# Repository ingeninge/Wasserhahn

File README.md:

# Wasserhahn

ATTENTION! This repository is only for testing! No production, and never will be.

MQTT controlled Motor Bulb Valve ESP8266 Arduino

Manufactor is END. Here is a link to the Datasheet: https://shop.end.de/armaturen/antriebe-und-zubehoer/elektrische-antriebe/ne034100-elektrischer-schwenkantrieb-30nm-230v-ac

Since my water tap in the garden was leaking and the repair would have included ripping down the building bricks, I asked a friend to build in a ball valve. 
On this I could mount a motor to open and close the garden water tap.
To control the motor I use a ESP8266-12 (WROOM-02) and two relays. The ESP uses 2 Inputs and 2 Outputs.
The schematic can be found in the folder images.
The Inputs are from the auxiliary isolated contacts from the motor. The contacts are closed ONLY at the end position of each turn.br>If both are open the valve is in between open and close.
The Outputs are controlling two relays. One for opening and one for closing the valve. The outputs are held active for 90 seconds.
<br>MQTT- protocol is used to control the garden water tap remotely.
First idea was to let it work with an Arduino Sketch, witch you can find in the sources. But then I figured out how to set up Tasmota to work with this Board and Motor. The workaround is: Tasmota [https://github.com/arendst/Tasmota] (I use Version 7.1) controls 2 relays - one for Opening and one for Closing the tap. The downside is, you will have to use two buttons or configure node-red with a function to control the state and switch between the states.<br>
For Programming see https://www.forward.com.au/pfod/ESP8266/GPIOpins/index.html GPIO0 and RST are on Jumper J5. GPIO2 is permanently pulled up via R8.
Todo: Remove copper under the antenna! Enable access to GPIO15 for programming mode or pull low permanent. update mill and drill files, mill, solder and test the layout. Release to public

The settings for Tasmota can be found in the Wiki https://github.com/ingeninge/Wasserhahn/wiki

BTW: I can control the bulb valve with a remote control in the garden, so I don't have to pull out my mobile to open the tap. [Remote control for Wasserhahn](https://github.com/ingeninge/ESP-Watertap-Remote)

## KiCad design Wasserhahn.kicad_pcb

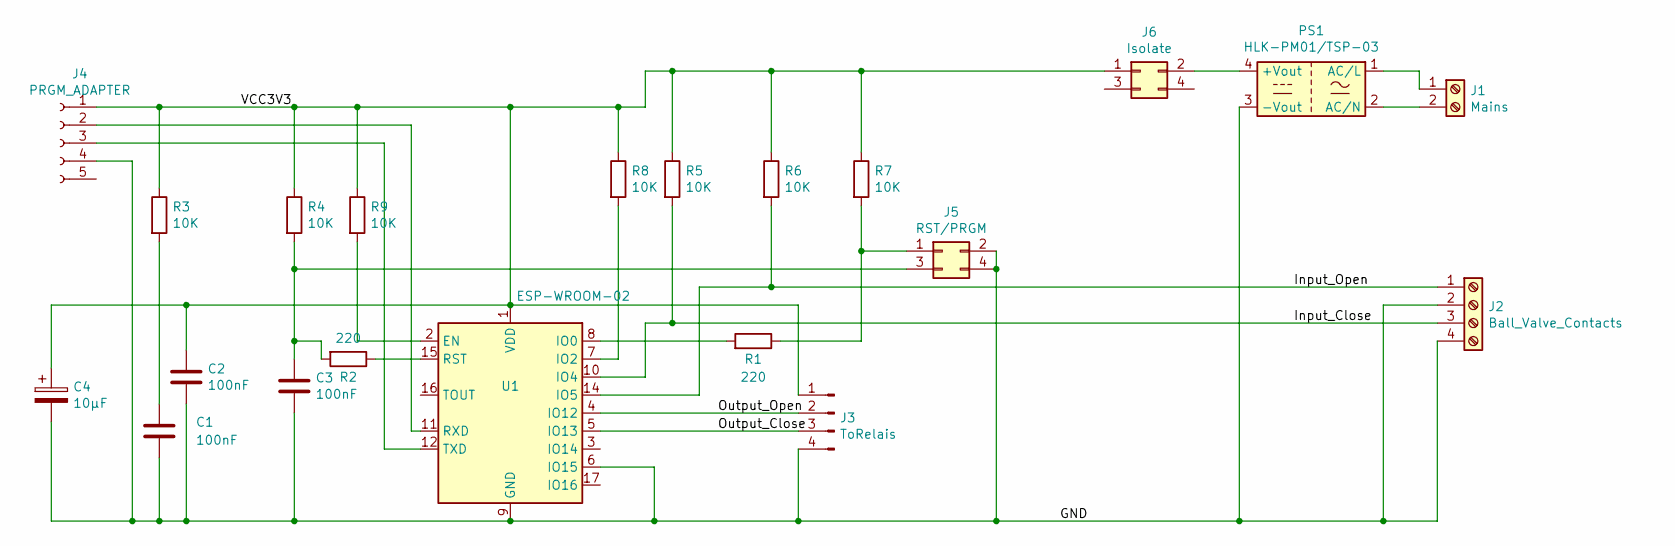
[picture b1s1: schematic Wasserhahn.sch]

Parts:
C1, C2, C3: 100nF; CP_Radial_D4.0mm_P2.00mm
C4: 10µF; CP_Radial_D6.3mm_P2.50mm
J1: Mains; TerminalBlock_Phoenix_PT-1,5-2-5.0-H_1x02_P5.00mm_Horizontal
J2: Ball_Valve_Contacts; TerminalBlock_Phoenix_PT-1,5-4-5.0-H_1x04_P5.00mm_Horizontal
J3: ToRelais; PinHeader_1x04_P2.54mm_Vertical
J4: PRGM_ADAPTER; PinHeader_1x05_P2.54mm_Vertical
J5: RST/PRGM; PinHeader_2x02_P2.54mm_Vertical
J6: Isolate; PinHeader_2x02_P2.54mm_Vertical
PS1: HLK-PM01/TSP-03; Converter_ACDC_HiLink_HLK-PMxx
R1, R2: 220; R_Axial_DIN0207_L6.3mm_D2.5mm_P10.16mm_Horizontal
R3, R4, R5, R6, R7, R8, R9: 10K; R_Axial_DIN0207_L6.3mm_D2.5mm_P10.16mm_Horizontal
U1: ESP-WROOM-02

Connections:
/GND: C1.2, C2.2, C3.2, C4.2, J2.2, J2.4, J3.4, J4.4, J5.2, J5.4, PS1.3 (-Vout), U1.6 (IO15), U1.9 (GND), U1.13 (GND), U1.18 (GND), U1.19 (GND)
/Input_Close: J2.3, R5.2, U1.10 (IO4)
/Input_Open: J2.1, R6.2, U1.14 (IO5)
/Output_Close: J3.3, U1.5 (IO13)
/Output_Open: J3.2, U1.4 (IO12)
/VCC3V3: C2.1, C4.1, J3.1, J4.1, J6.1, R3.1, R4.1, R5.1, R6.1, R7.1, R8.1, R9.1, U1.1 (VDD)
unnamed: C1.1, R3.2
unnamed: C3.1, J5.3, R2.2, R4.2
unnamed: J1.1, PS1.1 (AC/L)
unnamed: J1.2, PS1.2 (AC/N)
unnamed: J4.2, U1.11 (RXD)
unnamed: J4.3, U1.12 (TXD)
unnamed: J5.1, R1.1, R7.2
unnamed: J6.2, PS1.4 (+Vout)
unnamed: R1.2, U1.8 (IO0)
unnamed: R2.1, U1.15 (RST)
unnamed: R8.2, U1.7 (IO2)
unnamed: R9.2, U1.2 (EN)

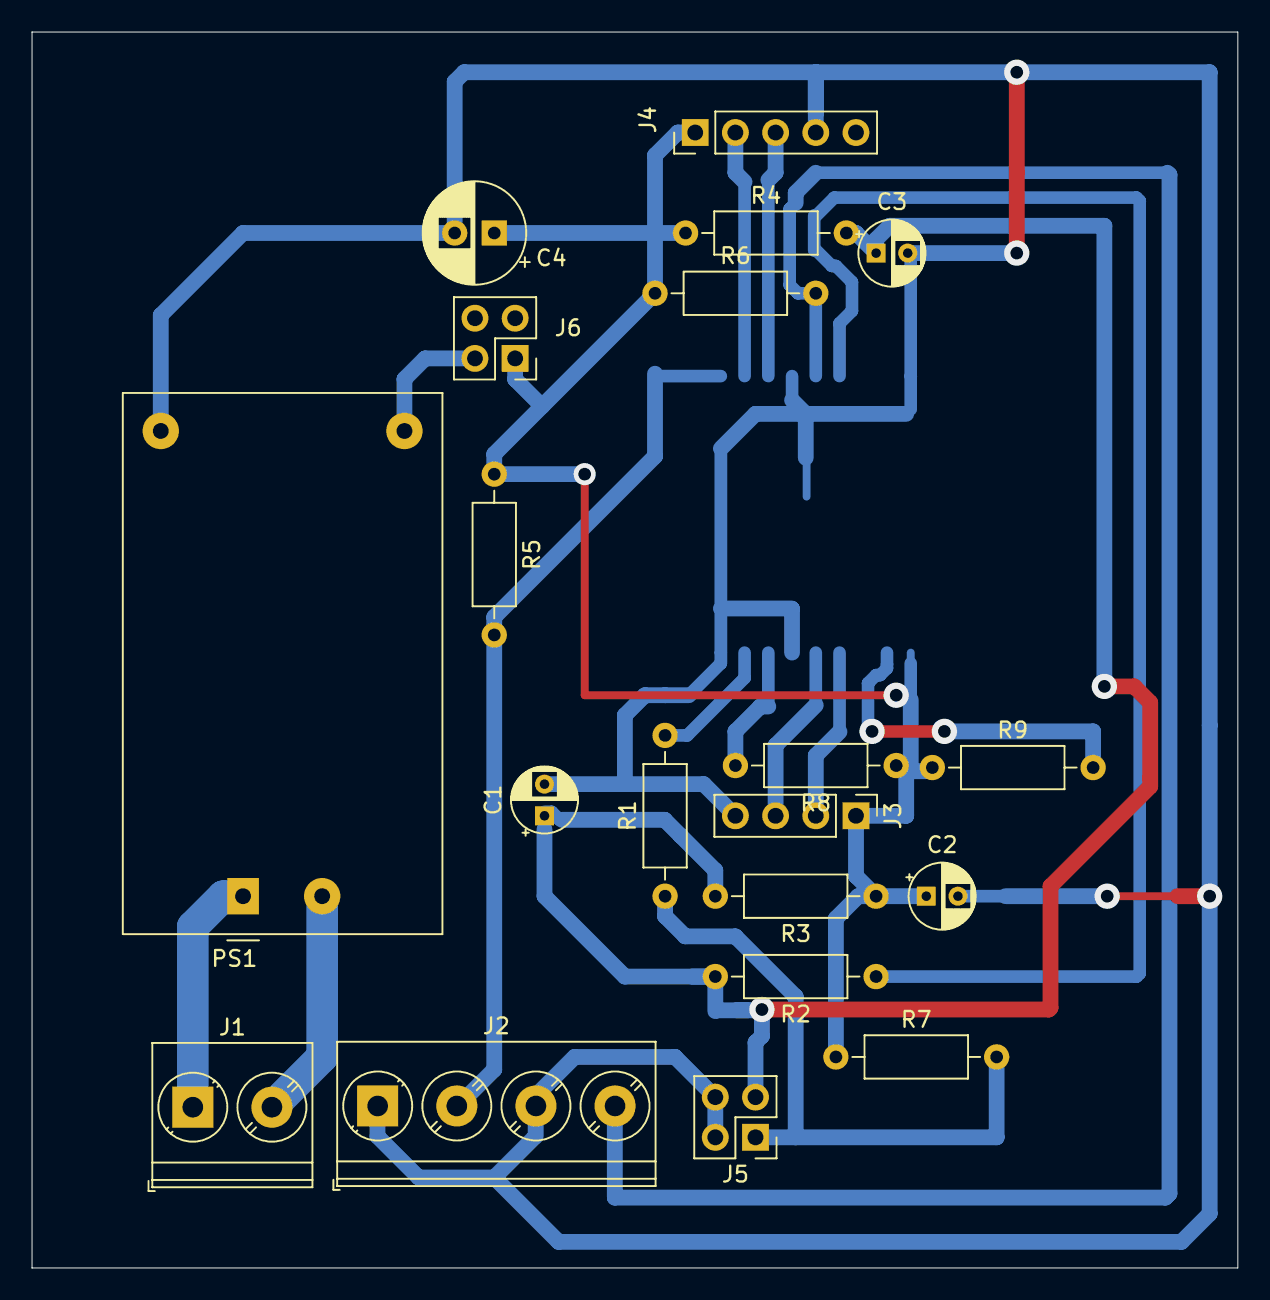
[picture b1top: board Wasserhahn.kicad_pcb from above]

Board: 2 copper layers, 76.2 x 78.1 mm, 21 parts (1 on the bottom side), 18 nets.

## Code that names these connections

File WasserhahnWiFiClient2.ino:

#include <PubSubClient.h>
#include <ESP8266WiFi.h>

/* Used ESP8266 WROOM-02 module from Pollin.de
Pin Name  Function  used_as
10  IO4   GPIO4     Input_Close Wasserhahn geschlossen, wenn auf GND
14  IO5   GPIO5     Input_Open  Wasserhahn geöffnet, wenn auf GND
04  IO12  GPIO12    Output_Open Schaltet das Relay zum Öffnen ein
05  IO13  GPIO13    Output_Close Schaltet das Relay zum Schließen ein

Usage:  mosquitto_pub -h 192.168.2.78 -t wasserhahn/set -m Status // returns a JSON-String: {"Close":0,"Open":1}
        mosquitto_pub -h 192.168.2.78 -t wasserhahn/set -m Close
        mosquitto_pub -h 192.168.2.78 -t wasserhahn/set -m Open

*/

#define INPUT_CLOSE 4
#define INPUT_OPEN 5
#define OUTPUT_OPEN 12
#define OUTPUT_CLOSE 13

#ifndef STASSID
#define STASSID "YourSSID"
#define STAPSK  "YourSecretKey"
#endif
const char* ssid     = STASSID;
const char* password = STAPSK;

char* topic = "wasserhahn/set";
char* server = "192.168.2.78";
char message_buff[100];

const char* host = "192.168.2.78";
const uint16_t port = 1883;
String payload = "";
// Der Motorkugelhahn hat 2 galvanisch getrennte kontakte. Einer schließt bei vollständig geschlossenem Kugelhahn,
// der zweite schließt bei vollständig geöffneten Kugelhahn. Dazwischen sind beide Kontakte offen
int status=0; //Status des Kugelhahns: 0=offen, 1=zu, 2=weder noch (beide Kontakte offen)
long lastReconnectAttempt = 0;

void Open() {
  if(!(digitalRead(INPUT_OPEN))) {
    Serial.println("Wasserhahn ist bereits auf");
    delay(100);
    Status();
    delay(100);
    exit;
  }
  else
  {
    Serial.println("Öffne Wasserhahn");
    while (digitalRead(INPUT_OPEN)) { 
      delay(100);
      digitalWrite(OUTPUT_OPEN, 1);
      //max 90sek
      delay(100);
    }
   }
    Serial.println("Wasserhahn voll geöffnet");
    delay(2000);
    digitalWrite(OUTPUT_OPEN, 0);
    delay(100);
    Status();
    delay(100);
}

void Close() {
  if(!(digitalRead(INPUT_CLOSE))) {
    Serial.println("Wasserhahn ist bereits zu");
    delay(100);
    Status();
    delay(100);
    exit;
  }
  else
  {
    Serial.println("Schließe Wasserhahn");
    while (digitalRead(INPUT_CLOSE)) { 
      delay(100);
      digitalWrite(OUTPUT_CLOSE, 1);
      //max 90sek
      delay(100);
    }
   }
    Serial.println("Wasserhahn voll geschlossen");
    delay(2000);
    digitalWrite(OUTPUT_CLOSE, 0);
    delay(100);
    Status();
    delay(100);
}

void callback(char* topic, byte* payload, unsigned int length) {
  // handle message arrived
  int i = 0;
  Serial.println("Message arrived:  topic: " + String(topic));
  Serial.println("Length: " + String(length,DEC));
  // create character buffer with ending null terminator (string)
  for(i=0; i<length; i++) {
    message_buff[i] = payload[i];
  }
  message_buff[i] = '\0';
  
  String msgString = String(message_buff);
  Serial.println("Payload: " + msgString);
  if (msgString.equals("Open")) {
    Open();
  } else if (msgString.equals("Close")) {
    Close();
  } else if (msgString.equals("Status")) {
    Status();
  }
}



String macToStr(const uint8_t* mac)
{
  String result;
  for (int i = 0; i < 6; ++i) {
    result += String(mac[i], 16);
    if (i < 5)
      result += ':';
  }
  return result;
}

WiFiClient wifiClient;
PubSubClient client(host, 1883, callback, wifiClient);

void setup() {
  //pinMode(pin,mode);
  pinMode(OUTPUT_CLOSE,OUTPUT);
  pinMode(OUTPUT_OPEN,OUTPUT);
  pinMode(INPUT_CLOSE,INPUT);
  pinMode(INPUT_OPEN,INPUT);
  digitalWrite(12,0);
  digitalWrite(13,0); //beide Relais aus
  
  Serial.begin(115200);

  // We start by connecting to a WiFi network

  //Serial.println();
  //Serial.println();
  Serial.print("Connecting to ");
  Serial.println(ssid);

  /* Explicitly set the ESP8266 to be a WiFi-client, otherwise, it by default,
     would try to act as both a client and an access-point and could cause
     network-issues with your other WiFi-devices on your WiFi-network. */
  WiFi.mode(WIFI_STA);
  WiFi.begin(ssid, password);

  while (WiFi.status() != WL_CONNECTED) {
    delay(500);
    Serial.print(".");
  }

  Serial.println("");
  Serial.println("WiFi connected");
  Serial.println("IP address: ");
  Serial.println(WiFi.localIP());
  Serial.println("Connecting to MQTT Broker");
  /*String clientName="Wasserhahn";
  uint8_t mac[6];
  WiFi.macAddress(mac);
  clientName += macToStr(mac);
  clientName += "-";
  clientName += String(micros() & 0xff, 16);

  Serial.print("Connecting to ");
  Serial.print(server);
  Serial.print(" as ");
  Serial.println(clientName);
    if (client.connect((char*) clientName.c_str())) {*/
    if (reconnect()) {
      Serial.println("Connected to MQTT broker");
      Serial.print("Topic is: ");
      Serial.println(topic);
    
      if (client.publish(topic, "hello from ESP8266")) {
        Serial.println("Publish ok");
      }
      else {
        Serial.println("Publish failed");
      }
    }
    else {
      Serial.println("MQTT connect failed");
      Serial.println("Will reset and try again...");
      abort();
    }
  if (client.connected()){
    Serial.print("Sending payload: ");
    Serial.println(payload);
    if (client.subscribe("wasserhahn/set")) {
      Serial.println("Subscripe OK");
    }
    else {
      Serial.println("Subscription failed");
    }
  }
}

void Status() {
  //create a JSON string
  payload = "{\"Close\":";
  payload += digitalRead(INPUT_CLOSE);
  payload += ",\"Open\":";
  payload += digitalRead(INPUT_OPEN);
  payload += "}";
  Serial.println("Status: " + payload);
  if (client.publish(topic, (char*) payload.c_str())) {
      Serial.println("Publish ok");
    }
    else {
      Serial.println("Publish failed Status()" +payload);
    }
    Serial.println("Ende Status()");
}

boolean reconnect() {
  String clientName="Wasserhahn";
  uint8_t mac[6];
  WiFi.macAddress(mac);
  clientName += macToStr(mac);
  clientName += "-";
  clientName += String(micros() & 0xff, 16);
  if (client.connect((char*) clientName.c_str())) {
    // Once connected, publish an announcement...
    client.publish("wasserhahn/set","reconnect");
    // ... and resubscribe
    client.subscribe("wasserhahn/set");
  }
  return client.connected();
}

void loop() {
  if (!client.connected()) {
    long now = millis();
    if (now - lastReconnectAttempt > 5000) {
      lastReconnectAttempt = now;
      // Attempt to reconnect
      if (reconnect()) {
        lastReconnectAttempt = 0;
        Serial.println("reconnected");
      }
    }
  } else {
    // Client connected

   //static int counter = 0;
  client.loop();
  //++counter;
  delay(50);
  }
  }

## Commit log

2020-04-26 Added Schematics in KiCAD Format, added outlines and milling files in g-code made with Flatcam.
2020-04-26 Addes pictures of the Motor
2020-04-26 Update README.md
    Text ....
2020-04-26 Added Arduino ino file and a picture of the schematic
2020-04-26 some changes in Wasserhahn.pro
2020-04-26 More code cleanup and credentials.h file for own WiFi Settings
2020-04-26 More code cleanup and Pins for NodeMCU
2020-04-26 Updated Board and Plot data
2020-04-26 Update README.md
    Added link to the product at END.
2020-05-15 optimized path in flatcam and widened the track width in kiCad
2020-05-15 Update README.md
    More todos
2020-05-16 width change for bigger tracks
2020-05-16 added connections for IO2, removed short circuit, swaped EN and RST on Jumper
2020-05-20 Update README.md
    Updated link to GPIO Programming Modes and a short description.
2020-05-23 GPIO15 pulled low, jumper to disconnect Power for flashing
2020-09-28 Update issue templates
2021-03-20 Update README.md
    Facelifting
2022-05-17 Update README.md
    Added link to the wiki
2023-03-12 Update README.md
    Added link to remote control
